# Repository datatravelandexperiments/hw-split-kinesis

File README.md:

Split Keyboard
==============

This is the hardware for modifying a [Kinesis contoured keyboard](http://kinesis-ergo.com/contoured.htm) into two separated units.

**This is a work in progress, and the hardware/software described here has not been shown to work correctly.**

The replacement controller communicates by SPI to an I/O expander on each keywell. Each keywell board plugs in to the keywell using staggered pin headers replacing the original FFC connector, and has a separate connector for the thumb keys. The rubber function keys are abandoned; I intend to use a FN key on the thumb matrix instead.

The controller (kctlspi) uses a [Micropendous 32U2](http://code.google.com/p/micropendous/wiki/Micropendous_32U2) board, because I happened to have a few on hand. Modifying it to use a similar device like a Teeny, Pro Micro, etc. should be straightforward.

The controller board has two Mini-DIN 8 jacks for the keywells. The pinout of these connectors is chosen such that the controller board could be repurposed as a dual PS/2 converter by swapping in Mini-DIN 6 connectors.

The controller also has two 6p6c jacks. The middle 4 pins match the pinout of foot switches for current Kinesis contoured keyboards; the other two supply V<sub>CC</sub> and GND to allow the possibility of active devices. The foot connectors are wired as a 2×3 matrix.

The controller board is sized to fit (half) a [readily available project box](http://www.google.com/search?q=24+70+110+aluminum+project+box). (Note: Many 6p6c jacks are too tall to fit this enclosure.)

The keywell boards (lctlspi and rctlspi) each use an MCP23S17 I/O expander. An MCP23017 could be substituted directly to use I<sup>2</sup>C rather than SPI. The chip's <span style="text-decoration:overline">RESET</span> and <span style="text-decoration:overline">CS</span> pins are present on the connector, but can be pulled up/down on the board instead.

The appropriate INTx pin is also present on the connector, so it should be possible to set up the I/O expander and put the controller to sleep until any key is pressed.

Left and right keywell controllers are different because the Kinesis keywells have different matrices. The correspondence between keywell signals and I/O expander pins is arbitrary (i.e. determined by layout convenience); that is, column 1 on the keywell does not correspond to pin 1 on an I/O port, and so on. Similarly the thumb pad connectors have the same pattern (GND, four columns, three rows) but the specific arrangement of rows and columns is arbitrary.

Schematics and boards are in [Eagle CAD](http://www.cadsoftusa.com/download-eagle/) format.

<!-- vim:set et sts=4 sw=4 linebreak ft=ghmarkdown: -->

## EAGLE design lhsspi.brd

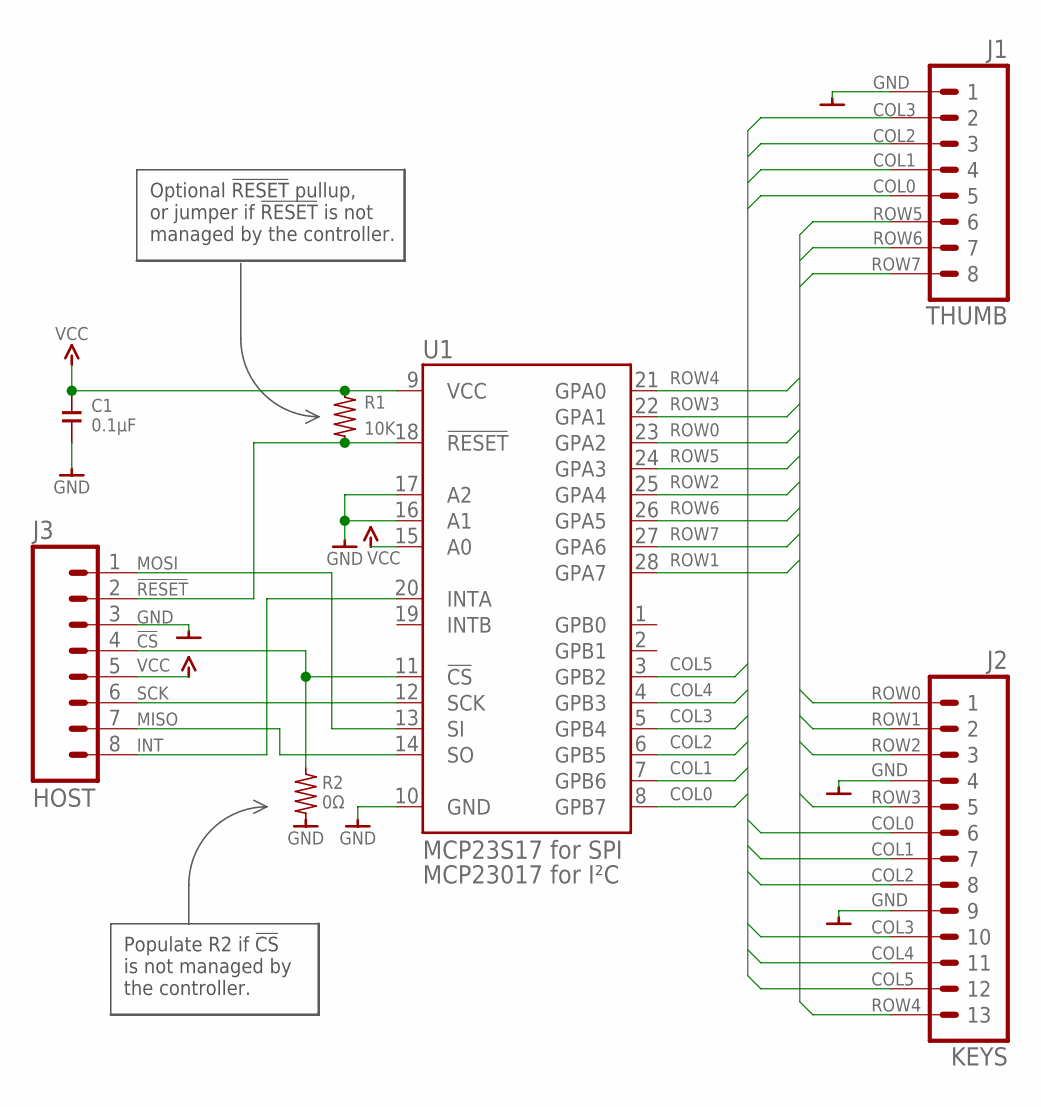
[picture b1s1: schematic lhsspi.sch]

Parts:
C1: 0.1µF; SMD-1206
J1: THUMB; J-8-2510
J2: KEYS; J-13-100-ALT-L
J3: HOST; J-8-2510
R1: 10K; SMD-1206
R2: 0Ω; SMD-1206
U1: MCP23S17 for SPI; IC-28-SOIC-300

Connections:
!CS: J3.4, R2.2, U1.11 (!CS)
!RESET: J3.2, R1.1, U1.18 (!RESET)
COL0: J1.5, J2.P6 (6), U1.8 (GPB7)
COL1: J1.4, J2.P7 (7), U1.7 (GPB6)
COL2: J1.3, J2.P8 (8), U1.6 (GPB5)
COL3: J1.2, J2.P10 (10), U1.5 (GPB4)
COL4: J2.P11 (11), U1.4 (GPB3)
COL5: J2.P12 (12), U1.3 (GPB2)
GND: C1.2, J1.1, J2.P4 (4), J2.P9 (9), J3.3, R2.1, U1.10 (GND), U1.16 (A1), U1.17 (A2)
INT: J3.8, U1.20 (INTA)
MISO: J3.7, U1.14 (SO)
MOSI: J3.1, U1.13 (SI)
ROW0: J2.P1 (1), U1.23 (GPA2)
ROW1: J2.P2 (2), U1.28 (GPA7)
ROW2: J2.P3 (3), U1.25 (GPA4)
ROW3: J2.P5 (5), U1.22 (GPA1)
ROW4: J2.P13 (13), U1.21 (GPA0)
ROW5: J1.6, U1.24 (GPA3)
ROW6: J1.7, U1.26 (GPA5)
ROW7: J1.8, U1.27 (GPA6)
SCK: J3.6, U1.12 (SCK)
VCC: C1.1, J3.5, R1.2, U1.9 (VCC), U1.15 (A0)

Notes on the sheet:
Populate R2 if !CS! is not managed by the controller.
MCP23017 for I²C
Optional !RESET! pullup, or jumper if !RESET! is not managed by the controller.

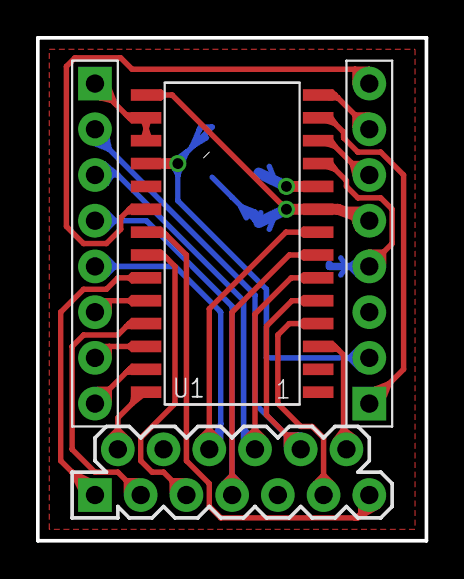
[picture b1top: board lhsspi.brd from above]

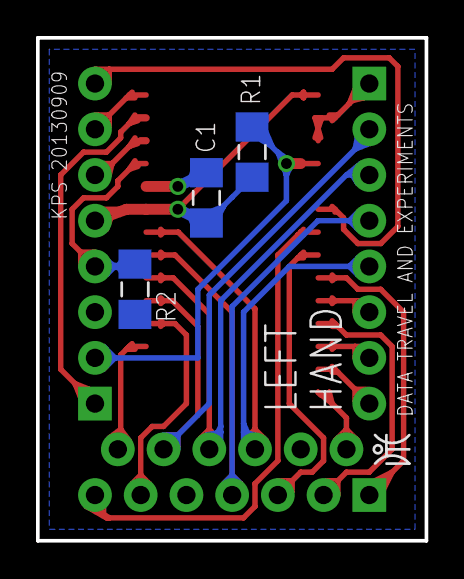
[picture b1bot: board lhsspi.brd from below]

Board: 2 copper layers, 21.6 x 27.9 mm, 7 parts (3 on the bottom side), 22 nets.

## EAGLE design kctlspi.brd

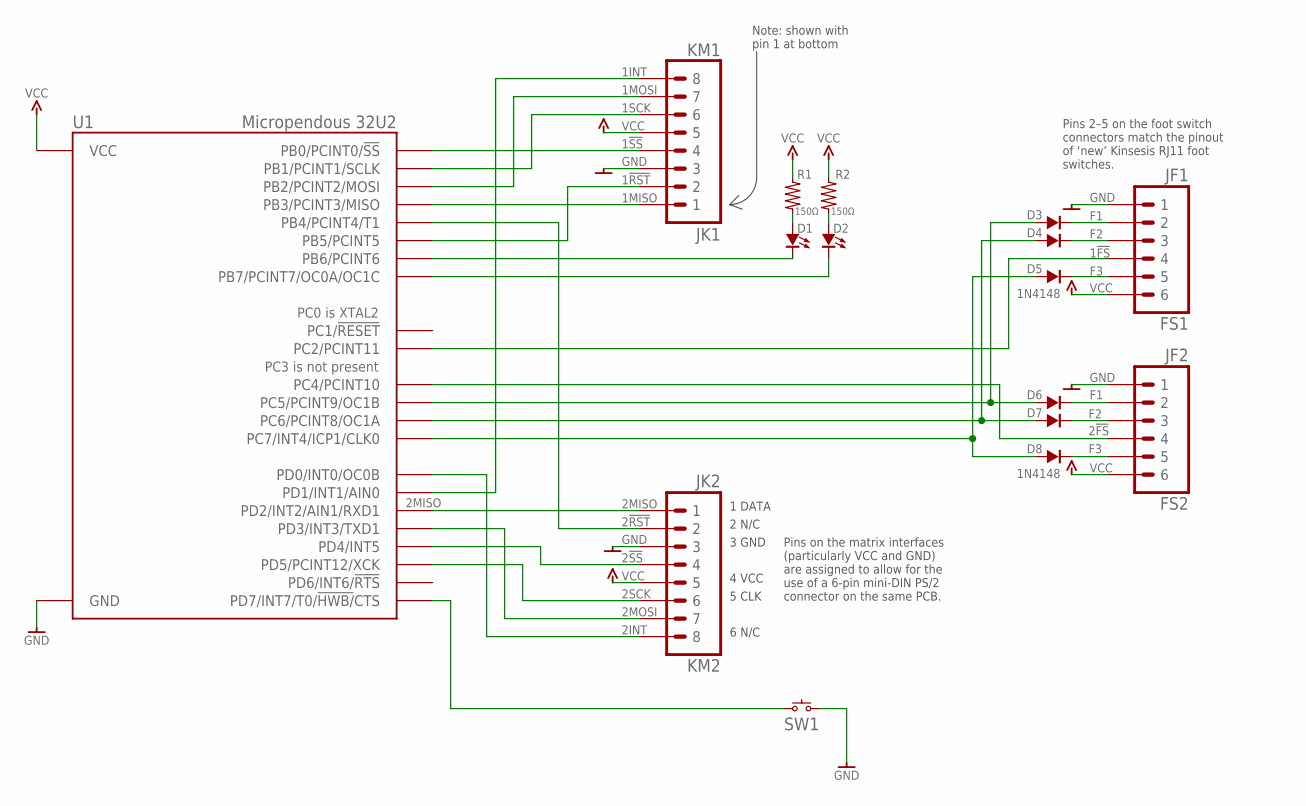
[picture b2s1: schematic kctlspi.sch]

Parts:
D1, D2: LED; 2H-100-P-EXTSS
D3, D4, D5, D6, D7, D8: 1N4148; 2H-300-P-SMALLSS
JF1: FS1; J-8-RJ12-TE5555163
JF2: FS2; J-8-RJ12-TE5555163
JK1: KM1; J-8-MINIDIN-KMD11
JK2: KM2; J-8-MINIDIN-KMD11
R1, R2: 150Ω; 2H-300-N-NOSS
SW1: SW-TACTILE-RA
U1: Micropendous 32U2; IC-ATMEGA32U2-NOOGROOVE

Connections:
1!FS: JF1.4, U1.PC2 (PC2/PCINT11)
1!RST: JK1.2, U1.PB5 (PB5/PCINT5)
1!SS: JK1.4, U1.PB0 (PB0/PCINT0/!SS)
1INT: JK1.8, U1.PD1 (PD1/INT1/AIN0)
1MISO: JK1.1, U1.PB3 (PB3/PCINT3/MISO)
1MOSI: JK1.7, U1.PB2 (PB2/PCINT2/MOSI)
1SCK: JK1.6, U1.PB1 (PB1/PCINT1/SCLK)
2!FS: JF2.4, U1.PC4 (PC4/PCINT10)
2!RST: JK2.2, U1.PB4 (PB4/PCINT4/T1)
2!SS: JK2.4, U1.PD4 (PD4/INT5)
2INT: JK2.8, U1.PD0 (PD0/INT0/OC0B)
2MISO: JK2.1, U1.PD2 (PD2/INT2/AIN1/RXD1)
2MOSI: JK2.7, U1.PD3 (PD3/INT3/TXD1)
2SCK: JK2.6, U1.PD5 (PD5/PCINT12/XCK)
F1: D3.A, D6.A, U1.PC5 (PC5/PCINT9/OC1B)
F2: D4.A, D7.A, U1.PC6 (PC6/PCINT8/OC1A)
F3: D5.A, D8.A, U1.PC7 (PC7/INT4/ICP1/CLK0)
GND: JF1.1, JF2.1, JK1.3, JK1.GND, JK2.3, JK2.GND, SW1.2, SW1.3 (GND), SW1.4 (GND), U1.GND
LED1: D1.C, U1.PB6 (PB6/PCINT6)
LED2: D2.C, U1.PB7 (PB7/PCINT7/OC0A/OC1C)
unnamed: SW1.1, U1.PD7 (PD7/INT7/T0/!HWB/!CTS)
unnamed: D3.C, JF1.2
unnamed: D4.C, JF1.3
unnamed: D5.C, JF1.5
unnamed: D8.C, JF2.5
unnamed: D7.C, JF2.3
unnamed: D6.C, JF2.2
unnamed: D2.A, R2.1
unnamed: D1.A, R1.1
VCC: JF1.6, JF2.6, JK1.5, JK2.5, R1.2, R2.2, U1.+5V (VCC)

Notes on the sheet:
1 DATA
2 N/C
3 GND
4 VCC
5 CLK
6 N/C
Pins on the matrix interfaces (particularly VCC and GND) are assigned to allow for the use of a 6-pin mini-DIN PS/2 connector on the same PCB.
Pins 2–5 on the foot switch connectors match the pinout of ‘new’ Kinsesis RJ11 foot switches.
Note: shown with pin 1 at bottom

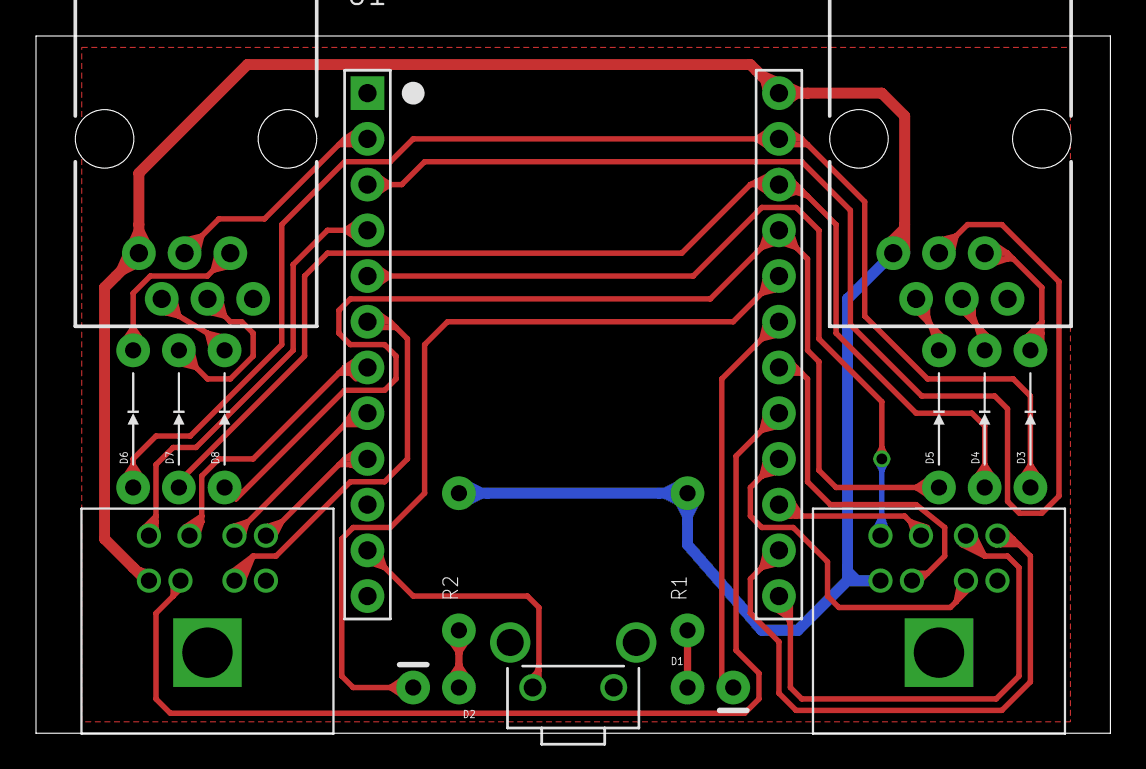
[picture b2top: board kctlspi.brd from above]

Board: 2 copper layers, 59.7 x 38.7 mm, 17 parts (1 on the bottom side), 30 nets.

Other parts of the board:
U$2: GLYPH-DT&E-100

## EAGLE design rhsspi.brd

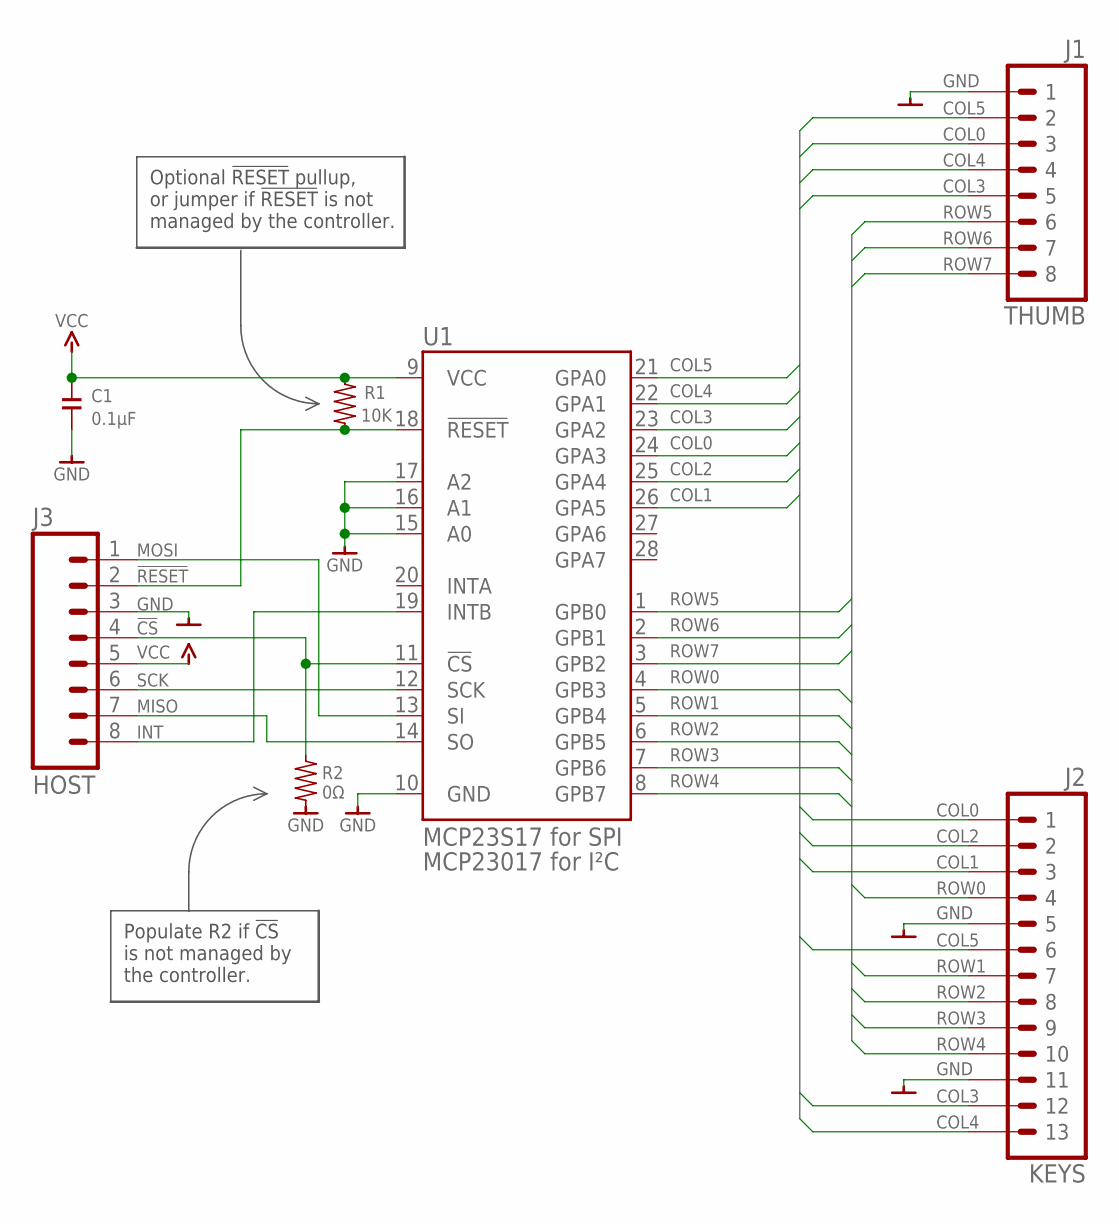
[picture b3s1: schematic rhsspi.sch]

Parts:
C1: 0.1µF; SMD-1206
J1: THUMB; J-8-2510
J2: KEYS; J-13-100-ALT-R
J3: HOST; J-8-2510
R1: 10K; SMD-1206
R2: 0Ω; SMD-1206
U1: MCP23S17 for SPI; IC-28-SOIC-300

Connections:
!CS: J3.4, R2.2, U1.11 (!CS)
!RESET: J3.2, R1.1, U1.18 (!RESET)
COL0: J1.3, J2.P1 (1), U1.24 (GPA3)
COL1: J2.P3 (3), U1.26 (GPA5)
COL2: J2.P2 (2), U1.25 (GPA4)
COL3: J1.5, J2.P12 (12), U1.23 (GPA2)
COL4: J1.4, J2.P13 (13), U1.22 (GPA1)
COL5: J1.2, J2.P6 (6), U1.21 (GPA0)
GND: C1.2, J1.1, J2.P5 (5), J2.P11 (11), J3.3, R2.1, U1.10 (GND), U1.15 (A0), U1.16 (A1), U1.17 (A2)
INT: J3.8, U1.19 (INTB)
MISO: J3.7, U1.14 (SO)
MOSI: J3.1, U1.13 (SI)
ROW0: J2.P4 (4), U1.4 (GPB3)
ROW1: J2.P7 (7), U1.5 (GPB4)
ROW2: J2.P8 (8), U1.6 (GPB5)
ROW3: J2.P9 (9), U1.7 (GPB6)
ROW4: J2.P10 (10), U1.8 (GPB7)
ROW5: J1.6, U1.1 (GPB0)
ROW6: J1.7, U1.2 (GPB1)
ROW7: J1.8, U1.3 (GPB2)
SCK: J3.6, U1.12 (SCK)
VCC: C1.1, J3.5, R1.2, U1.9 (VCC)

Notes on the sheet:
Populate R2 if !CS! is not managed by the controller.
Optional !RESET! pullup, or jumper if !RESET! is not managed by the controller.
MCP23017 for I²C

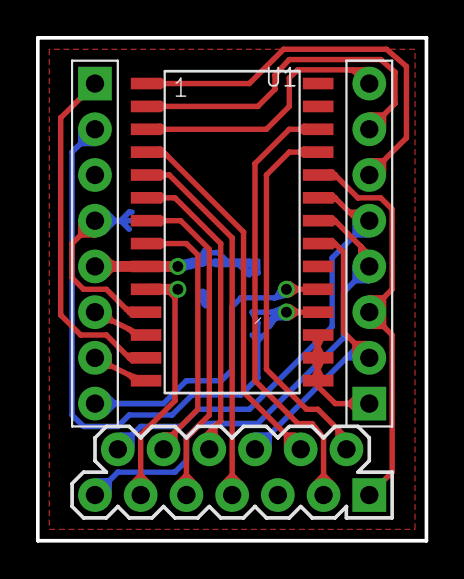
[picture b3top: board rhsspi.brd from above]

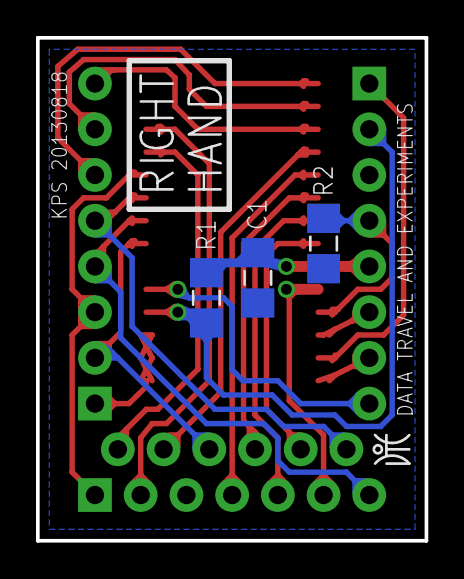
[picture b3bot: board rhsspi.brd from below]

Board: 2 copper layers, 21.6 x 27.9 mm, 7 parts (3 on the bottom side), 22 nets.

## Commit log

2013-09-10 Fiat lux.
2013-09-10 Move R1.
